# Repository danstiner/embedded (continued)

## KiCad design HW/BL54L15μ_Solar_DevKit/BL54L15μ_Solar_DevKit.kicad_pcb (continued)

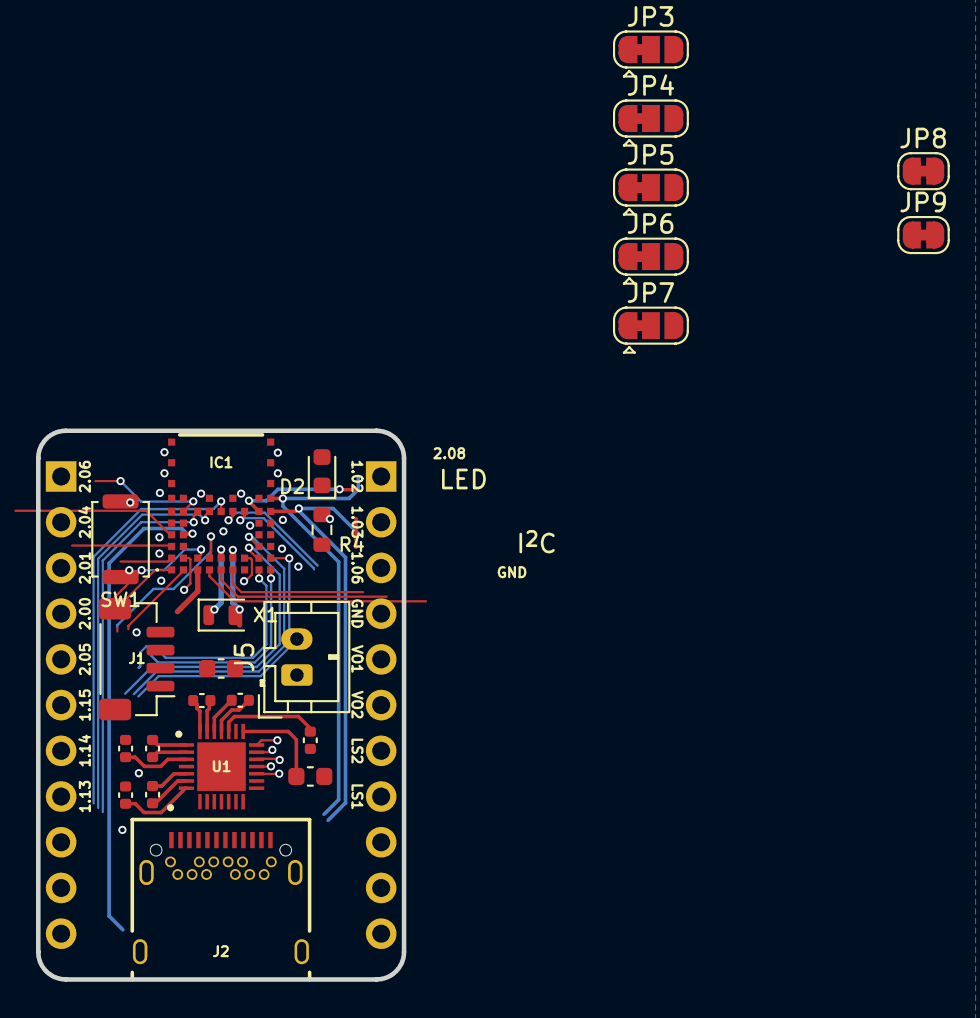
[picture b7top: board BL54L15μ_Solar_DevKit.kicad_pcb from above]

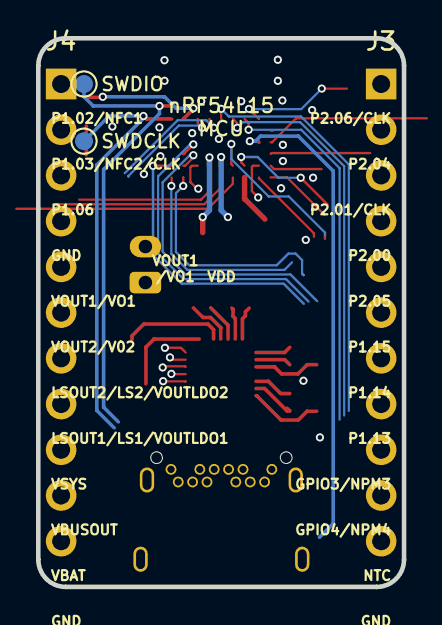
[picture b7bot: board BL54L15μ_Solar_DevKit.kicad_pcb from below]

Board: 4 copper layers, 20.3 x 30.5 mm, 29 parts (4 on the bottom side), 47 nets.

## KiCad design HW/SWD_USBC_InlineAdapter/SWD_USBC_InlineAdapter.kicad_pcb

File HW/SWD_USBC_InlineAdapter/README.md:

## Bill of materials

+-----------+-----+----------------------+--------------------+------------------------------------------------------------------------+
| Reference | Qty | Value                | Part Number        | Footprint                                                              |
+-----------+-----+----------------------+--------------------+------------------------------------------------------------------------+
| D1        | 1   | RED LED              | 150060SS75000      | Diode_SMD:D_0603_1608Metric                                            |
| J1        | 1   | Conn_ARM_JTAG_SWD_10 | FTSH-105-01-F-DV-K | Connector_PinHeader_1.27mm:PinHeader_2x05_P1.27mm_Vertical_SMD         |
| J2        | 1   | Conn_01x04           | 0532610471         | Connector_Molex:Molex_PicoBlade_53261-0471_1x04-1MP_P1.25mm_Horizontal |
| J3        | 1   | USB_C_Receptacle     | USB4056-03-A       | USB4056_03_A:GCT_USB4056-03-A_REVA2                                    |
| P1        | 1   | USB_C_Plug           | USB4155-03-C       | USB4155_03_C:GCT_USB4155-03-C_REVA                                     |
| R1        | 1   | 100Ω                 | RC0603FR-07100RL   | Resistor_SMD:R_0603_1608Metric                                         |
| R2        | 1   | 22kΩ ±5%             | RC0603FR-1322KL    | Resistor_SMD:R_0603_1608Metric                                         |
| R3        | 1   | 10kΩ ±5%             | RC0603FR-0710KL    | Resistor_SMD:R_0603_1608Metric                                         |
| R4,R5     | 2   | 5.1k                 | RC0603FR-075K1L    | Resistor_SMD:R_0603_1608Metric                                         |
+-----------+-----+----------------------+--------------------+------------------------------------------------------------------------+

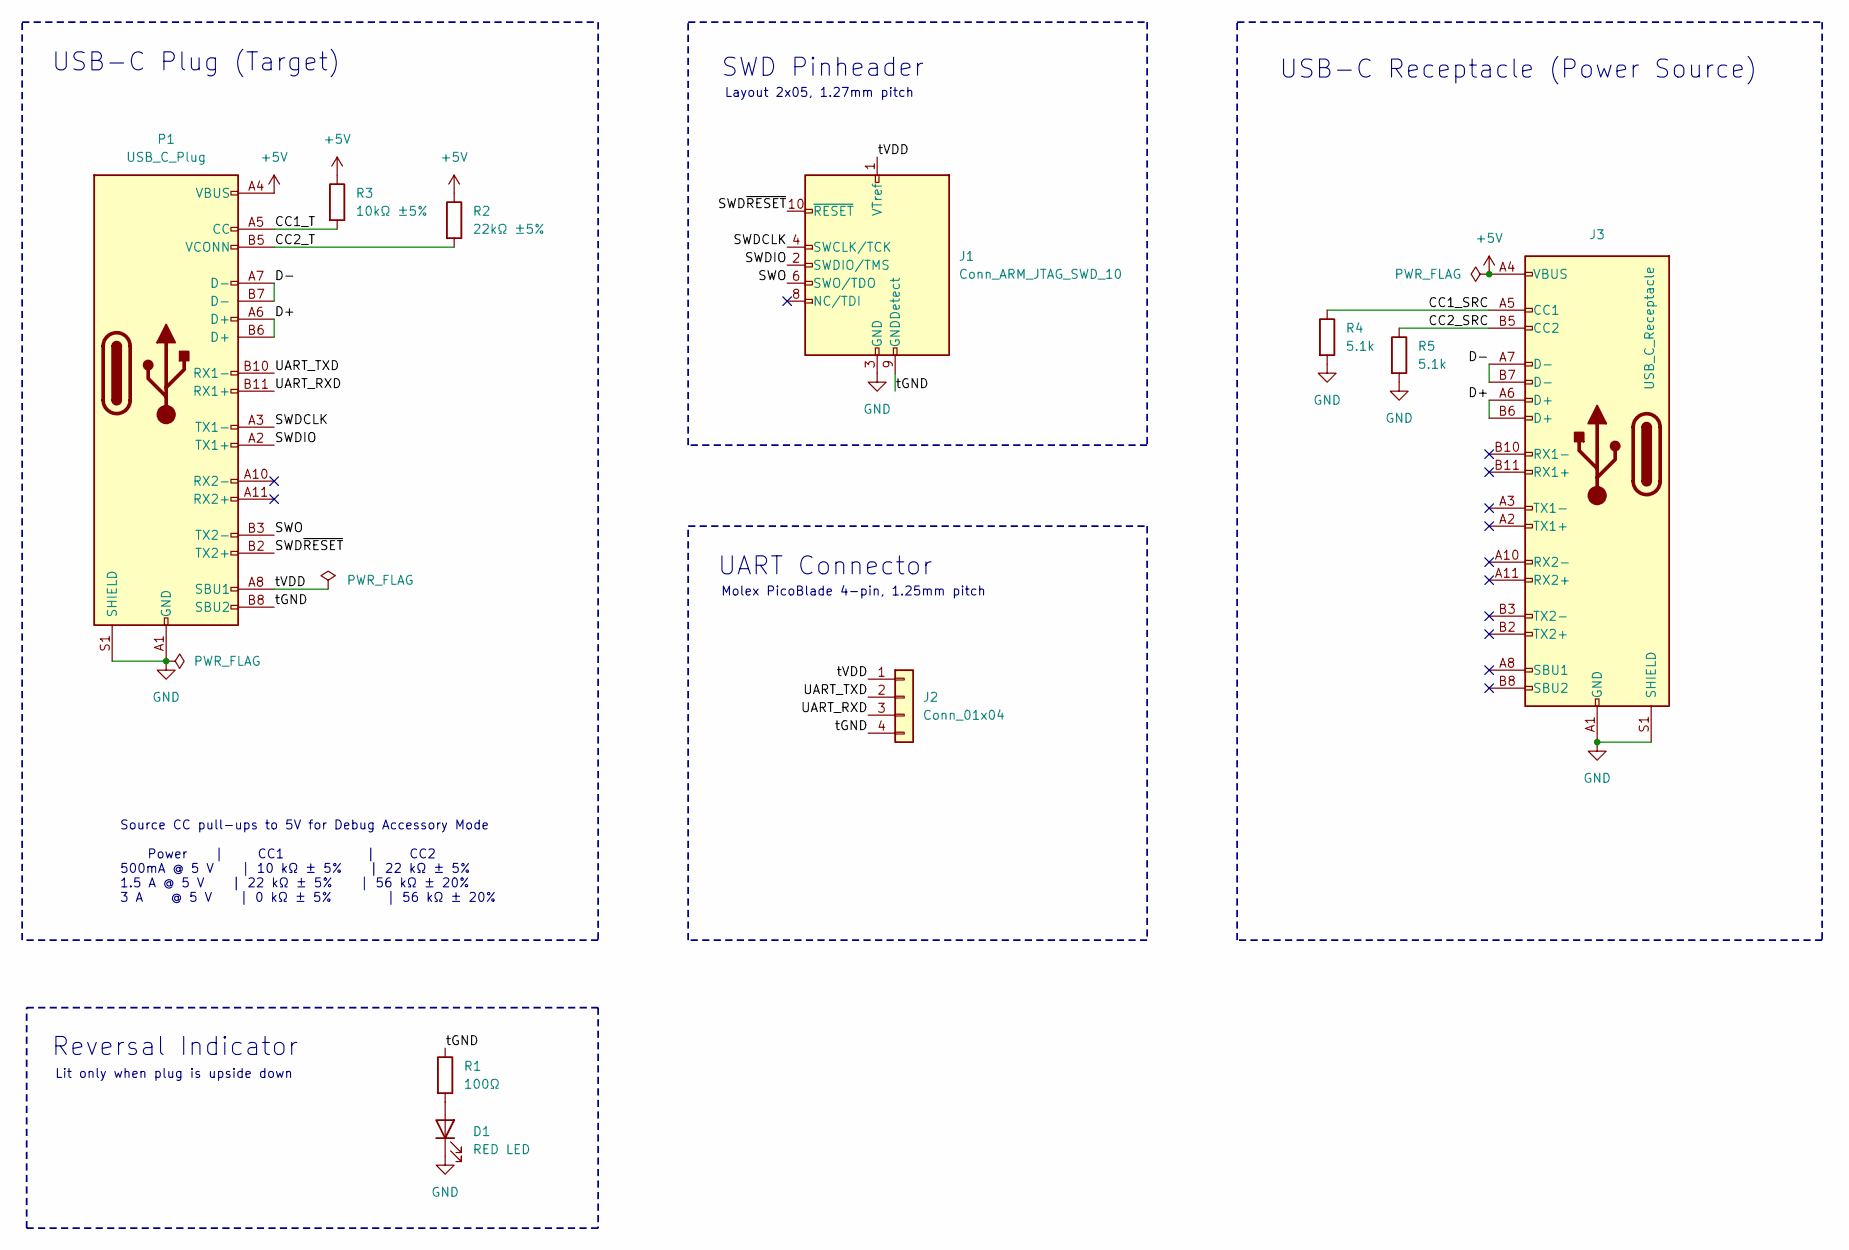
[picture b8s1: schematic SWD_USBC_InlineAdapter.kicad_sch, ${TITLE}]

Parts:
D1: RED LED; D_0603_1608Metric; Part Number 150060SS75000
J1: Conn_ARM_JTAG_SWD_10; PinHeader_2x05_P1.27mm_Vertical_SMD; Part Number FTSH-105-01-F-DV-K
J2: Conn_01x04; Molex_PicoBlade_53261-0471_1x04-1MP_P1.25mm_Horizontal; Part Number 0532610471
J3: USB_C_Receptacle; GCT_USB4056-03-A_REVA2; Part Number USB4056-03-A
P1: USB_C_Plug; GCT_USB4155-03-C_REVA; Part Number USB4155-03-C
R1: 100Ω; R_0603_1608Metric; Part Number RC0603FR-07100RL
R2: 22kΩ ±5%; R_0603_1608Metric; Digikey Part Number RC0603FR-1322KL
R3: 10kΩ ±5%; R_0603_1608Metric; Digikey Part Number RC0603FR-0710KL
R4, R5: 5.1k; R_0603_1608Metric; Digikey Part Number 311-5.10KHRCT-ND

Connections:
+5V: J3.A4 (VBUS), J3.A9 (VBUS), J3.B4 (VBUS), J3.B9 (VBUS), P1.A4 (VBUS), P1.A9 (VBUS), P1.B4 (VBUS), P1.B9 (VBUS), R2.1, R3.1
/CC1_SRC: J3.A5 (CC1), R4.1
/CC1_T: P1.A5 (CC), R3.2
/CC2_SRC: J3.B5 (CC2), R5.1
/CC2_T: P1.B5 (VCONN), R2.2
/D+: J3.A6 (D+), J3.B6 (D+), P1.A6 (D+), P1.B6 (D+)
/D-: J3.A7 (D-), J3.B7 (D-), P1.A7 (D-), P1.B7 (D-)
/SWDCLK: J1.4 (SWCLK/TCK), P1.A3 (TX1-)
/SWDIO: J1.2 (SWDIO/TMS), P1.A2 (TX1+)
/SWD~RESET: J1.10 (~RESET), P1.B2 (TX2+)
/SWO: J1.6 (SWO/TDO), P1.B3 (TX2-)
/UART_RXD: J2.3, P1.B11 (RX1+)
/UART_TXD: J2.2, P1.B10 (RX1-)
/tGND: J1.9 (GNDDetect), J2.4, P1.B8 (SBU2), R1.1
/tVDD: J1.1 (VTref), J2.1, P1.A8 (SBU1)
GND: D1.1 (K), J1.3 (GND), J1.5 (GND), J3.A1 (GND), J3.A12 (GND), J3.B1 (GND), J3.B12 (GND), J3.S1 (SHIELD), P1.A1 (GND), P1.A12 (GND), P1.B1 (GND), P1.B12 (GND), P1.S1 (SHIELD), R4.2, R5.2
unnamed: D1.2 (A), R1.2

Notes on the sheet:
SWD Pinheader
Layout 2x05, 1.27mm pitch
Reversal Indicator
Lit only when plug is upside down
USB-C Receptacle (Power Source)
Source CC pull-ups to 5V for Debug Accessory Mode Power | CC1 | CC2 500mA @ 5 V | 10 kΩ ± 5% | 22 kΩ ± 5% 1.5 A @ 5 V | 22 kΩ ± 5% | 56 kΩ ± 20% 3 A @ 5 V | 0 kΩ ± 5% | 56 kΩ ± 20%
USB-C Plug (Target)
UART Connector
Molex PicoBlade 4-pin, 1.25mm pitch

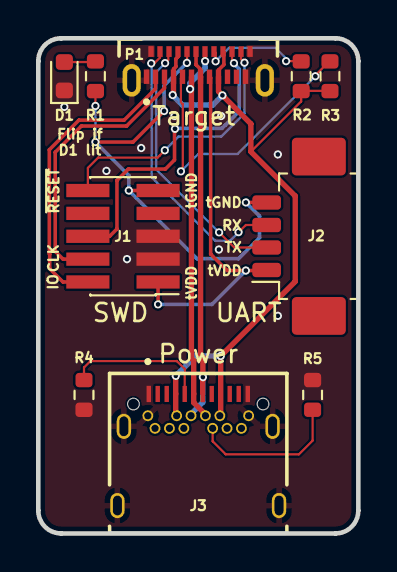
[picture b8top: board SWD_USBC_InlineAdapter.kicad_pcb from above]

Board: 4 copper layers, 17.8 x 27.5 mm, 10 parts (0 on the bottom side), 17 nets.

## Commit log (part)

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2026-03-05 -extra-arg
2026-03-05 Extract to script with correct escaping
2026-03-05 Better quoting
2026-03-05 Comment cleanup
2026-03-05 README cleanup
2026-03-05 Drop CHIP_ICD_SIT_SLOW_POLL_LIMIT override
2026-03-05 Cleanup comment
2026-03-05 Add missing path dep
2026-03-05 Use commit hash for always rolling ccache
2026-03-10 stcc4_enter_sleep command
2026-03-10 Sleep stcc4 between readings
2026-03-10 Simplify reading sensor values
2026-03-10 Further sensor read cleanup
2026-03-10 clang-format
2026-03-13 Fix STCC4 pressure compenstation and sleep
2026-03-14 STCC4 Force Calibration trigger
2026-03-14 fix mcubook usage examples and add more
2026-03-14 Use 1mA avg usage for npm2100 fuel gauging
2026-03-14 Enabled runtime power management
2026-03-14 Add PM=y, though it doesn't do anything on this platform
2026-03-14 Cleanup unused instances
2026-03-14 Oops we're using gpiote20 somehow?
2026-03-14 Move bluetooth/IP support into project board config
2026-03-14 Add back LFXO to 2026v3 board rev
2026-03-14 Remove unnecessary disables
2026-03-14 Re-order init
2026-03-14 Debugging power usage
2026-03-14 Always leave i2c pins biased up.
    Without this we leak around 100uA for a SHT4X on the I2C bus
2026-03-14 Power down unused memory
2026-03-15 Move LDOSW suspend
2026-03-15 Power down RAM on matter side
2026-03-15 Keep pull-ups during I2C sleep to prevent floating CMOS inputs on peripherals
2026-03-15 SWB to USB adapter bill of materials
2026-03-15 Formatting
2026-03-15 Linting script
2026-03-15 Fix formatting
2026-03-16 Config to disable STCC4/BME688, fix for drain when LDOSW disabled
2026-03-16 STCC4 STOP_CONTINUOUS command and cleanup
2026-03-16 Start LDOSW in ULP mode
2026-03-16 Log cleanup
2026-03-16 Remove gas heater workaround
2026-03-18 Log pin test as INF
2026-03-18 Enable LFXO on devkit 2026v2 boards
2026-03-18 Cleanup kconfig overlays
2026-03-18 Use 10uA as idle power estimate
2026-03-18 Disable PMIC
2026-03-18 cmake to include board mcuboot overlay
2026-03-18 Rename board vendor
2026-03-18 Power optimization and Matter integration for hygrometer
    Power management:
    - Keep I2C pull-ups active during sleep to prevent ~100uA leak from
    floating CMOS inputs
    - Power down unused RAM
    - Start LDOSW in ULP mode to prevent ~2mA leak in HP mode
    - Use 10uA as idle power estimate
2026-03-21 BTHome and STCC4 improvements
    - Init STCC4 on boot
    - Fix STCC4 forced recalibration to be concurrent with main loop
    - Fix devkit advertising battery=0% and voltage=0mV on boot
    - Advertise BTHome packet ID for tracking update freshness
    - Reduce advertising interval to 4-4.5s for power savings
    - Simplify MCUboot release mode configs
2026-03-29 Prototype firmware for air quality and thread border router board
2026-03-29 github action
2026-03-29 Make tidy script generic
2026-03-29 lint fixes
2026-03-29 Shorten advertisement in devkit
2026-03-31 First pass at modeling two electrode probe
2026-04-28 BL54L15μ Hygrometer 2026v4 with leak sensing
    - Switch to CR2 battery
    - Drop power-hungry STCC4/BME688 sensors
    - Circular design with M1.2 mounting holes
2026-05-16 WIP snap fit tests
2026-06-01 Basic case model for Hygrometer 2026v3 board
2026-06-01 airhub HW prototype
2026-06-02 v4 support, including leak sense
2026-06-02 README build line fixup
2026-06-02 Oversample battery voltage a bit
2026-06-02 Coarse battery health in bthome advertisements
2026-06-02 Rename SHT45 -> SHT4X
2026-06-02 Fix leak sense to not have internal pull-up
2026-06-02 Bump to ncs v3.3.0
2026-06-02 Zigbee R23 add-on
2026-06-03 Zigbee prototype
2026-06-03 Name attribute and power savings
2026-06-04 Additional attributes
2026-06-04 Log reporting interval on startup
2026-06-05 Zigbee report interval config
2026-06-05 Additional logging
2026-06-06 Cleanup
2026-06-06 Simplify extern C handling for zboss
2026-06-06 Report battery soc
2026-06-08 zigbee router
2026-06-09 Cleanup matter support
2026-06-09 Use a CSPRNG
2026-06-09 Remove zigbee build
2026-06-09 cache size
2026-06-09 board rev matter config
2026-06-09 Cleanup board revs
2026-06-09 Set CONFIG_BT_DEVICE_NAME by board rev
2026-06-09 Cleanup readme
2026-06-09 Do not build factory data partition
2026-06-10 doc updates
2026-06-10 Do not generate factory data partition
2026-06-10 factory flash text update
2026-06-10 Update product name
2026-06-10 docs update
2026-06-10 Fix init order of CO2 server instance
2026-06-10 Minimal immediate-mode RTT logs
2026-06-10 Reproducible factory data provisioning
2026-06-10 Add DTS for button on 2026v3
2026-06-10 Pairing mode LED and button fix
2026-06-10 Enable DK library for LED support
2026-06-10 Always log STCC4 reading
2026-06-10 Async STCC4 conditioning on boot
2026-06-10 Product name tweak
2026-06-10 Fix SN typo
2026-06-10 Default sensor values to NULL
2026-06-11 Comments
2026-06-11 highest
2026-06-11 Treat invalid reads as null measurements
2026-06-15 Simplify OTA script
2026-06-16 Fix -Dmcuboot_EXTRA_CONF_FILE
2026-06-16 Save space by reducing CONFIG_BOOT_MAX_IMG_SECTORS
2026-06-16 CONFIG_MCUBOOT_LOG_LEVEL_DBG
2026-06-16 Remove incorrect CONFIG_LOG_MODE_MINIMAL=y
2026-06-16 Redulce space with CONFIG_CHIP_LOG_SIZE_OPTIMIZATION
2026-06-17 devicetree partition layout
2026-06-17 Migrate away from partition manager to device tree partitions
2026-06-18 Separate RTT shell to save power
2026-06-18 rtt shell
2026-06-18 nullable bat voltage/soc
2026-06-18 Simplify soc_health
2026-06-18 ota script improvements
2026-06-18 Cleanup sensor_read_battery
2026-06-19 Improve leak sense
2026-06-19 Rename fake vendor to "local" for now
2026-06-20 fix clang-format version pin
2026-06-20 Add chip shell
2026-06-20 co2 recalibration
2026-06-21 target ppm kconfig and co2 recal/hard reset
2026-06-21 12 hr continuous after hard reset
2026-06-21 Small Claude.md
2026-06-21 STCC4_BYPASS_DISCARDS consistency
2026-06-24 Rewrite of STCC4 compensation
2026-06-24 Formatting and comment cleanup
2026-06-25 Cleanup partition dtsi to work on nrf54l15dk
2026-06-28 Cleanup DK partitional layout handling
2026-06-28 tidy
2026-06-29 Simplify tidy.sh
